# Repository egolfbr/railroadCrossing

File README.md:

# RailRoadCrossing
Arduino based railroad crossing replica 
## Table of Contents
## Table of Contents
**[Introduction](#Introduction)**<br>
**[Gather Materials](#Gather-Matierals)**<br>
**[Building](#Building)**<br>
**[Programming](#Programming)**<br>
**[Conclusion](#Conclusion)**<br>

## Introduction
With the coronavirus sending students home for the rest of the semester (spring 2020), I found myself with a lot of extra time on my hands and lots of parts that I have never used.I recalled that the theme for this years VBS at my church is a railroad theme and my idea was born. I decided that I was going to make a railroad crossing signal. You know the ones with the moving arm, sound and blinking lights. It seemed a little easy especially since I am a junior electrical engineering student so I set off to work, needless to say, I encountered many errors and problems that made this a not an “easy” project. Certainly not a “plug and go” anyway lets get started.

## Gather Materials
Step 1: Gather materials. 
* 3x Arduino UNOs - $23/ea (arduino.cc)
* 2x microswitches - $2/ea* (microcenter)
* 2x pushbuttons - $0.10/ea (digikey)
* 2x 8Ohm-1W speakers - $2.95/ea (microcenter)
* 1x adafruit sound effects board $30/ea (adafruit)
* 2x neopixel ring (16LEDs)
* 1x barrel jack
* 1x 5V 3A power supply
* 2x 10K ohm resistors
* Jumper wire
* 2x MOSFET N-ch 30V transistor
* 2x MOSFET P-ch 27A transistor
* 1x 555 timer
* 1x 125V 3A fuse
* 2x 10000pf ceramic capacitor
* 2x 1n4004 diode
* 1x 19rpm economy brush pur motor
* 1x 4mm shaft mount 32 pitch 16T gear
* 1x 32 pitch 64T 1” bore gear

Estimated total cost:
	For those who do not have any previous material the estimated total cost is about $276. This does not include shipping and tax as you will most likely end up ordering from multiple different places. Websites such as Amazon may make it cheaper. I ended up spending just under $100 on parts that I didn’t have. PCB ordering is also not factored into this cost. I usually order PCBs from China. This means that I have to order a minimum of 10 boards per design. Thus with SeedStudio, I will have to pay around $5 for each design as well as shipping and tax for each one. I also included what the cost would be had I been contracted by a client to build this device. I used a simple google search of the median income of an electrical engineer to base my calculation for the per hour pay. 

You may be wondering why I use so many microcontrollers for a relatively simple process. I was limited by 2 main factors in this build, materials that I had, and money. Now, using 3 micro controllers seems like a costly thing to do and it is. However, I was lucky enough to receive a donation of parts last year which included about 10 arduinos. So having these extra controllers was a huge relief because it allowed me to make this project more parallel. In other words, I have multiple processes running at the same time across multiple devices. I will get into this more as I explain the circuit in the next section, but as some of you may guess, running certain processes takes time and if I want to say blink LEDs and move a motor at the same time, there will be a delay in the circuit. I may make a video example of what I am talking about for those who are confused. 
## Building 
Step 2: build the circuit.
	The most important thing to remember here is to CONNECT ALL GROUND PINS. Also pin numbers are arbitrary. There is no specific reason I choose any of the digital IO pins. The SDA and SCL pins however must remain on A4 and A5 respectively. There are other places to connect these pins on other versions of the arduino UNO but I like to use these pins because they are universal on the UNO models. 
	Additionally, due to my lack of knowledge in EAGLE I will attach hand drawn circuit schematics for parts of the circuit that parts aren’t readily available for on EAGLE so that you have them and I will work on updating the EAGLE file so that there is one complete schematic file that can be downloaded. On the hand-drawn circuits, any node names that are the same on the EAGLE file are connected. For example, on the board labeled SOUND, there is a pin labeled SOUNDPIN. On the hand-drawn schematic there is also a SOUNDPIN, that means that those nodes are connected. Also there is a portion of the circuit that is simplified. For the neopixel rings I only included 2xsingle LED schematics. In reality each of those single LEDs is a whole 16 LED ring. Connections are the same though because you are connecting the last LED on the first ring with the first LED on the second ring.
	So like I mentioned before, I chose to use multiple arduino so that I could make this a parallel design. The other option for me would be to use an FPGA since those are much easier to parallelize however, I did not have the equipment to debug that device. So that is why I ended up with lots of arduinos. First I was planning on just using two arduinos but found that trying to quickly change cases in the state machine (the code implementation that I will discuss next), this proved too slow. This is because in the code I called a function to flash the neopixel LEDs and this takes time. 
Let me take a break here and explain why I chose neopixel rings. Realistically I would’ve used lots of small 3-5mm LEDs and not these rings. That is because with the single diodes, you can simply connect and disconnect power to blink the LEDs. This would lead me to do a hardware implementation of the blinking lights. This can be done a couple ways. I saw a way to do it with a switching NPN transistor similar to the 2n2222 (please correct me if I am wrong). I imagine that this can be done with a crystal oscillator or a 555 timer circuit. I did have several 555 timers available to use but unfortunately I only had about 20 THT LEDs. So that is the main reason that I used the rings. I also find the rings brighter. The big downside is that they must remain plugged into the programmed pin (in my case pin 6). 
Okay so I grabbed a new arduino so that I could put a dedicated LED flashing code on it to flash during 3 of the 4 states of the state machine. Even though this one arduino is slower than the rest in terms of reading/displaying data on the SDA line, it is more acceptable because little kids love LEDs and who cares if the LEDs are on for a second or 2 longer than necessary. It is much more desirable and safer than say having the master arudino not read the digital pins while the motor is still running trying to push the arm higher and stalling the motor and maybe causing a fire. 
For the sound arduino I used the Adafruit sound effects board and some low powered speakers. This was the plug and go part of the project. There is a tutorial on how to use this board on Adafruit’s website which I will post a link to. The sound file is a simple MP3 that I downloaded for free (link below). You don’t have to include a sound portion to this project as it does get rather annoying but I always enjoy sound effects.
For the motor I just used the sound arduino because the sound doesn’t take a lot of time because it is just toggling a pin high and low. I used an attached link for the build of a custom H-bridge motor driver with variable speed and direction. The attached link had 95% of the circuit already designed so that was very helpful. The only portion that I personally designed and built was making it “programmable.” This means that instead of using a physical switch to change direction and to power the motor on and off, I used signals from the arduino dedicated to that function. The main issue is that I needed a SPDT switch that doesn’t require human interaction. Again, limited by supplies I landed on a 5V relay. A relay can be used similar to a 2n2222 transistor in that it can control higher voltage and amperage signals with a common 5V or 3.3V signal depending on the relay. In this case I didn’t need it to control a high voltage or current, just the fact that I needed it to be programmable. So the relay portion of the circuit controls the direction because for an H-bridge, if one side is connected to the power supply, and the other side is at ground, then the motor spins one way and if you switch those signals then you can make it spin the other way. To control the status of the motor (whether it is on or off) I simply used another N-Channel MOSFET transistor. Below are some images of the full circuit. First is the full motor dirver all wired up with a PWM signal and Hbridge, then just the PWM signal generator (555 timer circuit), then the master controller which takes inputs from sensors and buttons, the LED circuit which is just some neoPixel Rings, and finally, the audio circuit. I used an Adafruit sound effects board to shorten the project and bring the complexity down a bit.
<p align="center">

<p align="center">

<p align="center">

<p align="center">

<p align="center">

## Programming
Step 3: Code the Arduino’s
	For this project I implemented a state machine. This is just so that it is easier to organize on paper, in the code and in my head. Basically a state machine is a machine whose outputs are decided by which state it is in and the state is decided by the inputs. That is just a very general description. State machines are all around us from traffic lights to elevators, so it is very useful to get to know how to program one and how they work. Typically, these are implemented with an FPGA but they can really be implemented with anything. My code is heavily commented so I don’t anticipate this to be a long section. 

State Diagram:

<p align="center">

The state diagram helps visualize what is supposed to happen. This helps when errors occur etc.  
A key note that I found out debugging my code is that the break statements are very important when using switch statements. Without these the code won’t run properly. I tried to do some basic research on the switch statements because I had used switch statements before but I had not looked into why we use breaks. What I came up with was that breaks basically prevent the code from running the following case.

## Conclusion

Overall this project took me about 12 hours to complete. I worked for about 2-3 hrs every couple days or so for about 3 weeks. However, if you had all the parts I imagine that this would take maybe an afternoon or two. The main thing that slowed me down were simple software errors mainly. The hardware was rather simple once I got the parts. There were a few instances where I had to improvise and come up with some of my own stuff (see motor power and motor direction without buttons) but again most of the information was already available I just had to synthesize it in a certain way. If I were to do this again  I would try to implement this with an FPGA and more hardware solutions like the 555 timer circuit for the LEDs. I would like to print PCBs for this project to make it more professional as well. Furthermore I would like to see if there is a way to use less arduinos. The one thing that I will probably actually do as an extension is that I will add another arduino or raspberry pi to read telemetry data from the circuit and based on that master data determine if it is necessary to shut the circuit off. I already need to wire battery packs to all the arduinos to a master switch to turn them all on  at the same time and having that switch or another controlled via microcontroller shouldn’t be too hard. I will also add a screen to display current information relevant to the well being of the circuit. 
	
video link: https://youtu.be/l8aVLoQLqr0

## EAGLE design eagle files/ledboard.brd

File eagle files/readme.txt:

These files are free software: you can redistribute it and/or modify
    it under the terms of the GNU General Public License as published by
    the Free Software Foundation, either version 3 of the License, or
    (at your option) any later version.

    This program is distributed in the hope that it will be useful,
    but WITHOUT ANY WARRANTY; without even the implied warranty of
    MERCHANTABILITY or FITNESS FOR A PARTICULAR PURPOSE.  See the
    GNU General Public License for more details.

    You should have received a copy of the GNU General Public License
    along with this program.  If not, see <https://www.gnu.org/licenses/>.
    
    These eagle files were prototyped and designed by Brian Egolf.

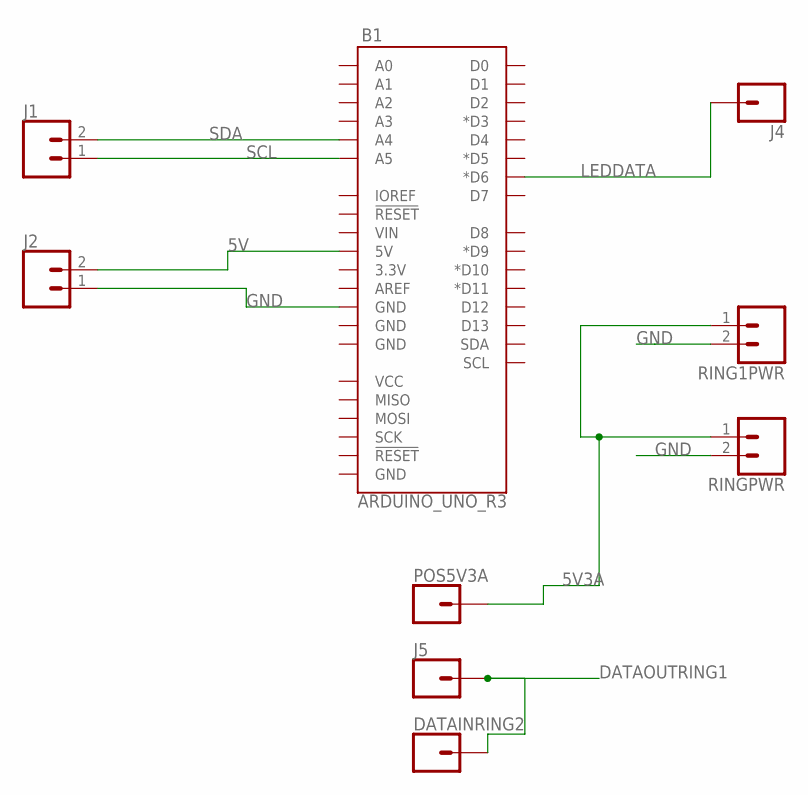
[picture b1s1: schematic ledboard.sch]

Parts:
B1: ARDUINO_UNO_R3; ARDUINO_R3
DATAINRING2: CONN_01; 1X01
J1, J2: CONN_023.5MM; SCREWTERMINAL-3.5MM-2
J4, J5: CONN_01; 1X01
POS5V3A: CONN_01; 1X01
RING1PWR: CONN_023.5MM; SCREWTERMINAL-3.5MM-2
RINGPWR: CONN_023.5MM; SCREWTERMINAL-3.5MM-2

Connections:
5V: B1.5V, J2.2
5V3A: POS5V3A.1, RING1PWR.1, RINGPWR.1
DATAOUTRING1: DATAINRING2.1, J5.1
GND: B1.GND@4 (GND), J2.1, RING1PWR.2, RINGPWR.2
LEDDATA: B1.D6 (*D6), J4.1
SCL: B1.A5, J1.1
SDA: B1.A4, J1.2

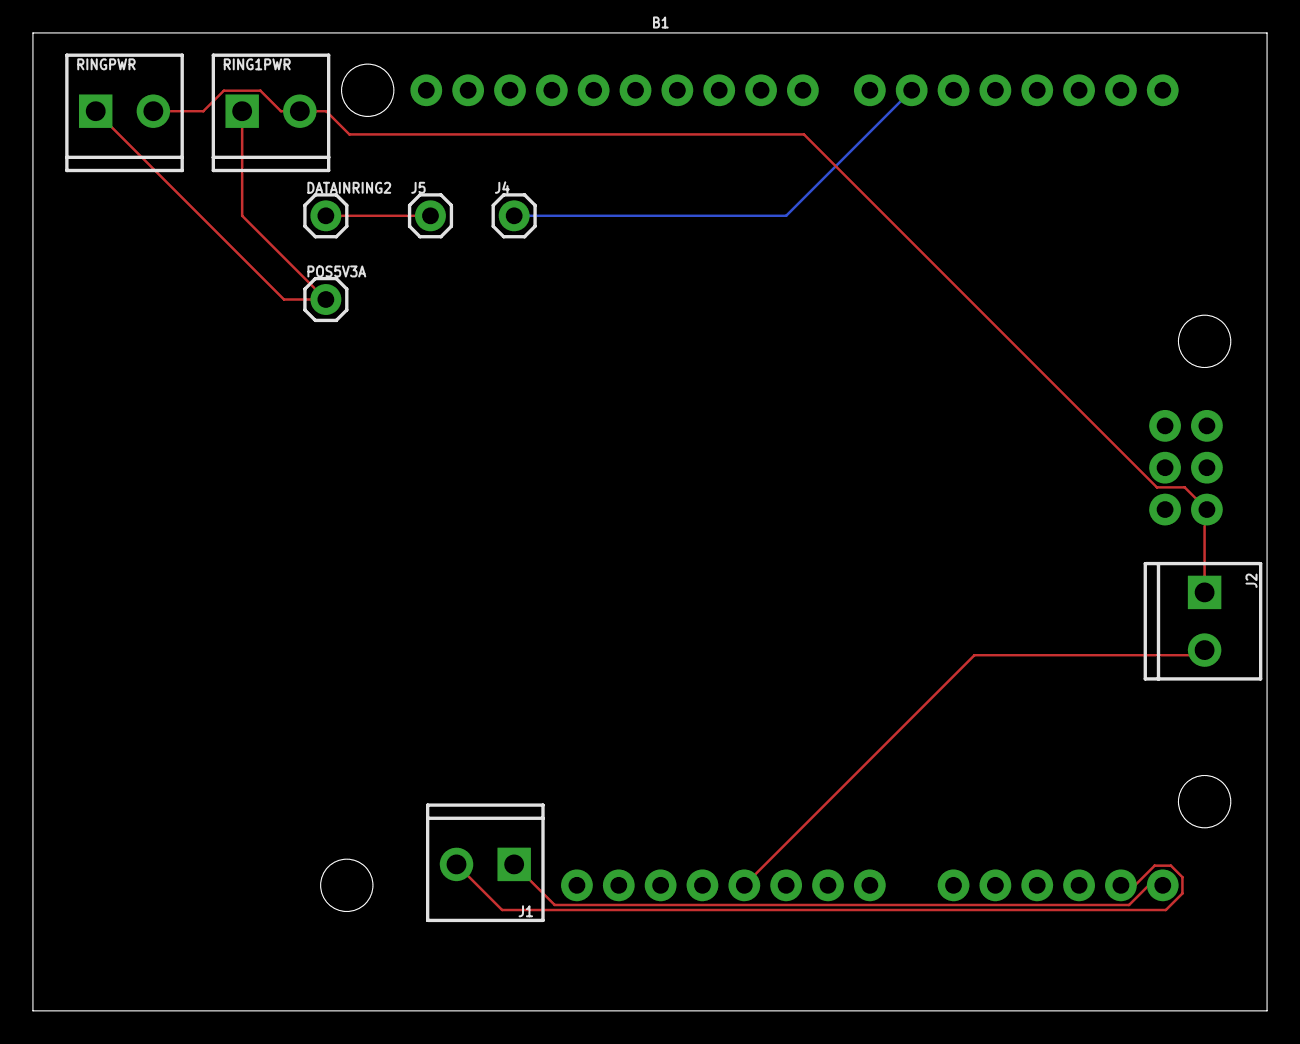
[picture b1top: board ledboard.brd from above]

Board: 2 copper layers, 74.9 x 59.4 mm, 9 parts (0 on the bottom side), 7 nets.

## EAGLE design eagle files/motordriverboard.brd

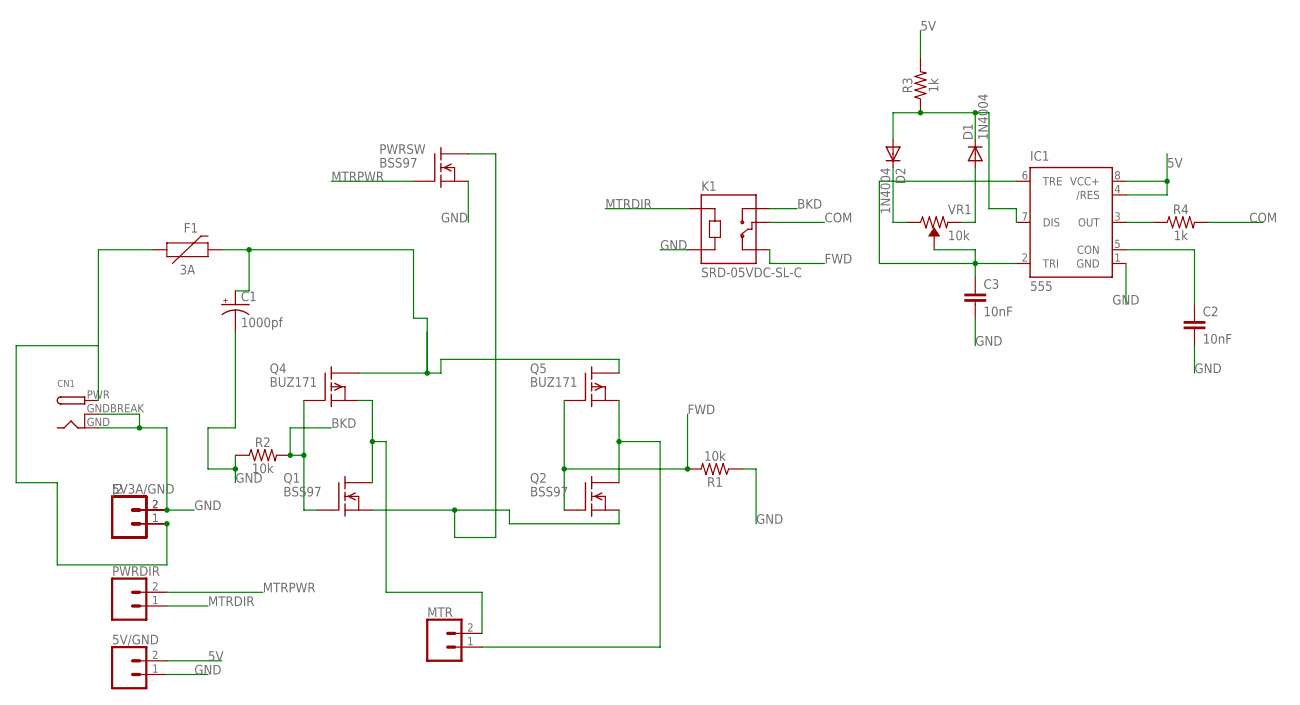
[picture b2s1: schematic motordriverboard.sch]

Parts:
5V3A/GND, 5V/GND: CONN_023.5MM; SCREWTERMINAL-3.5MM-2
C1: 1000pf; E5-6
C2, C3: 10nF; CAP-PTH-10MM
CN1: DCBARRELPTH; DCJACK_2MM_PTH
D1, D2: 1N4004; DO41-10
F1: 3A; PTH
IC1: 555; DIP08
J2: CONN_023.5MM; SCREWTERMINAL-3.5MM-2
K1: SRD-05VDC-SL-C; RELAY_SRD-05VDC-SL-C
MTR: CONN_023.5MM; SCREWTERMINAL-3.5MM-2
PWRDIR: CONN_023.5MM; SCREWTERMINAL-3.5MM-2
PWRSW: BSS97; TO202
Q1, Q2: BSS97; TO202
Q4, Q5: BUZ171; TO220
R1, R2: 10k; AXIAL-0.3
R3, R4: 1k; AXIAL-0.3
VR1: 10k; TRIMPOT-PTH-3386U

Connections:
5V: 5V/GND.2, IC1.4 (/RES), IC1.8 (VCC+), R3.P$2 (2)
BKD: K1.NO, Q1.3 (G), Q4.1 (G), R2.P$2 (2)
COM: K1.COM, R4.P$2 (2)
FWD: K1.NC, Q2.3 (G), Q5.1 (G), R1.P$2 (2)
GND: 5V3A/GND.2, 5V/GND.1, C1.-, C2.2, C3.2, CN1.GND, CN1.GNDBREAK, IC1.1 (GND), J2.2, K1.A2, PWRSW.1 (S), R1.P$1 (1), R2.P$1 (1)
MTRDIR: K1.A1, PWRDIR.1
MTRPWR: PWRDIR.2, PWRSW.3 (G)
unnamed: C2.1, IC1.5 (CON)
unnamed: IC1.3 (OUT), R4.P$1 (1)
unnamed: C3.1, IC1.2 (TRI), IC1.6 (TRE), VR1.2 (WIPER)
unnamed: C1.+, F1.P$2 (2), Q4.2 (D), Q5.2 (D)
unnamed: D1.C, D2.A, IC1.7 (DIS), R3.P$1 (1)
unnamed: MTR.1, Q2.2 (D), Q5.3 (S)
unnamed: MTR.2, Q1.2 (D), Q4.3 (S)
unnamed: PWRSW.2 (D), Q1.1 (S), Q2.1 (S)
unnamed: 5V3A/GND.1, CN1.PWR, F1.P$1 (1), J2.1
unnamed: D2.C, VR1.3 (CW)
unnamed: D1.A, VR1.1 (CCW)

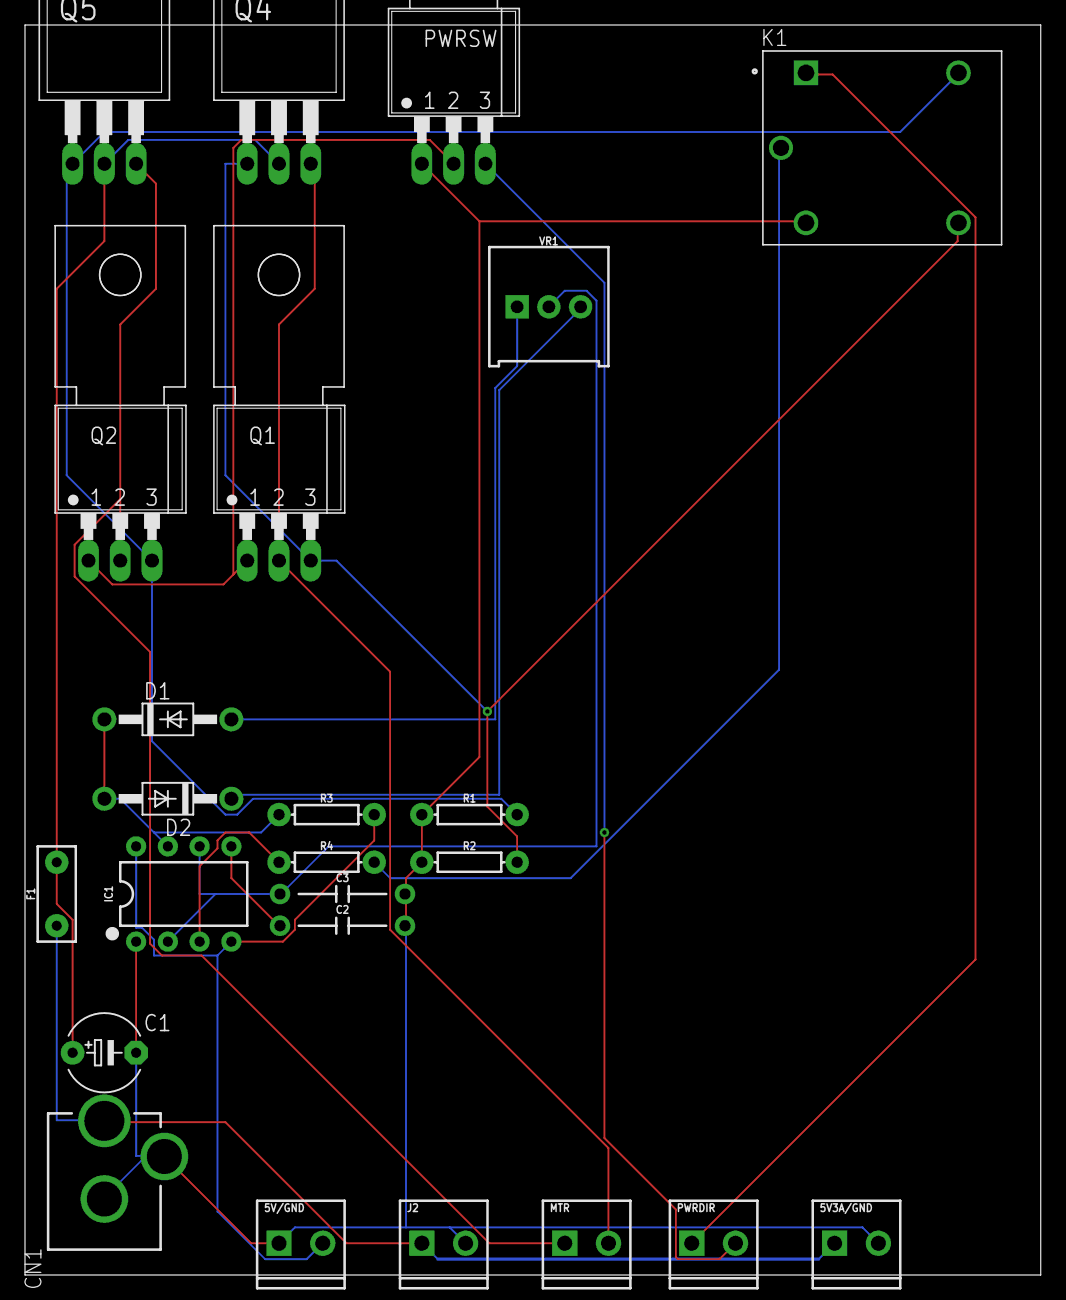
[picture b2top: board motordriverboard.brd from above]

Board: 2 copper layers, 81.3 x 100.0 mm, 24 parts (0 on the bottom side), 18 nets.

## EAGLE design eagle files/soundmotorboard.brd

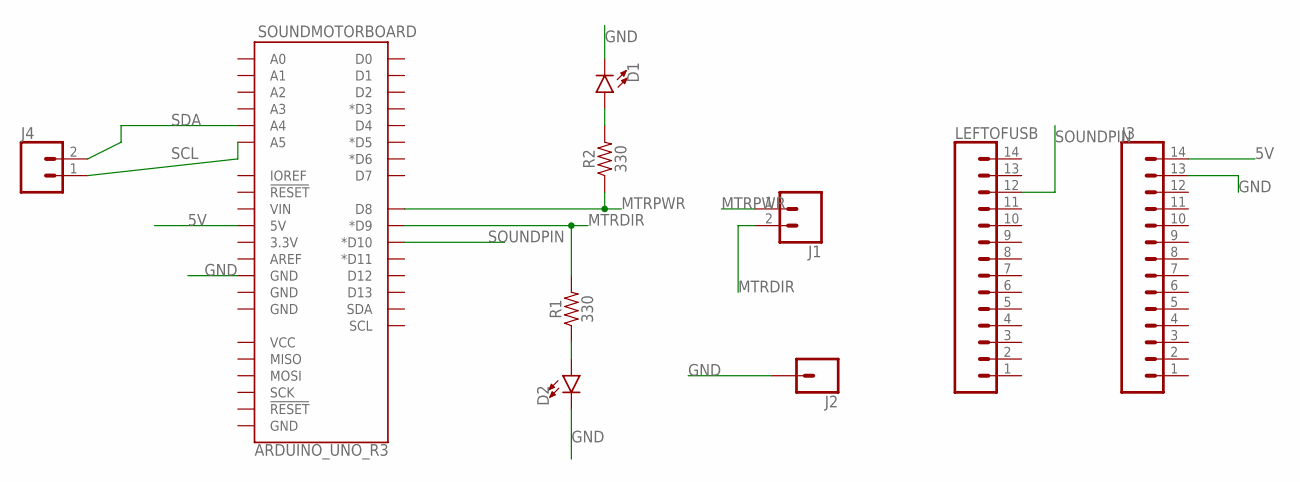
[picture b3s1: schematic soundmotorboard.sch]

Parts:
D1, D2: LED5MM; LED_5MM
J1: CONN_023.5MM-NO_SILK; SCREWTERMINAL-3.5MM-2-NS
J2: CONN_01; 1X01
J3: CONN_14; 1X14
J4: CONN_023.5MM; SCREWTERMINAL-3.5MM-2
LEFTOFUSB: CONN_14; 1X14
R1, R2: 330; AXIAL-0.3
SOUNDMOTORBOARD: ARDUINO_UNO_R3; ARDUINO_R3

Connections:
5V: J3.14, SOUNDMOTORBOARD.5V
GND: D1.K (C), D2.K (C), J2.1, J3.13, SOUNDMOTORBOARD.GND@4 (GND)
MTRDIR: J1.2, R1.P$2 (2), SOUNDMOTORBOARD.D9 (*D9)
MTRPWR: J1.1, R2.P$1 (1), SOUNDMOTORBOARD.D8
unnamed: D1.A, R2.P$2 (2)
unnamed: D2.A, R1.P$1 (1)
SCL: J4.1, SOUNDMOTORBOARD.A5
SDA: J4.2, SOUNDMOTORBOARD.A4
SOUNDPIN: LEFTOFUSB.12, SOUNDMOTORBOARD.D10 (*D10)

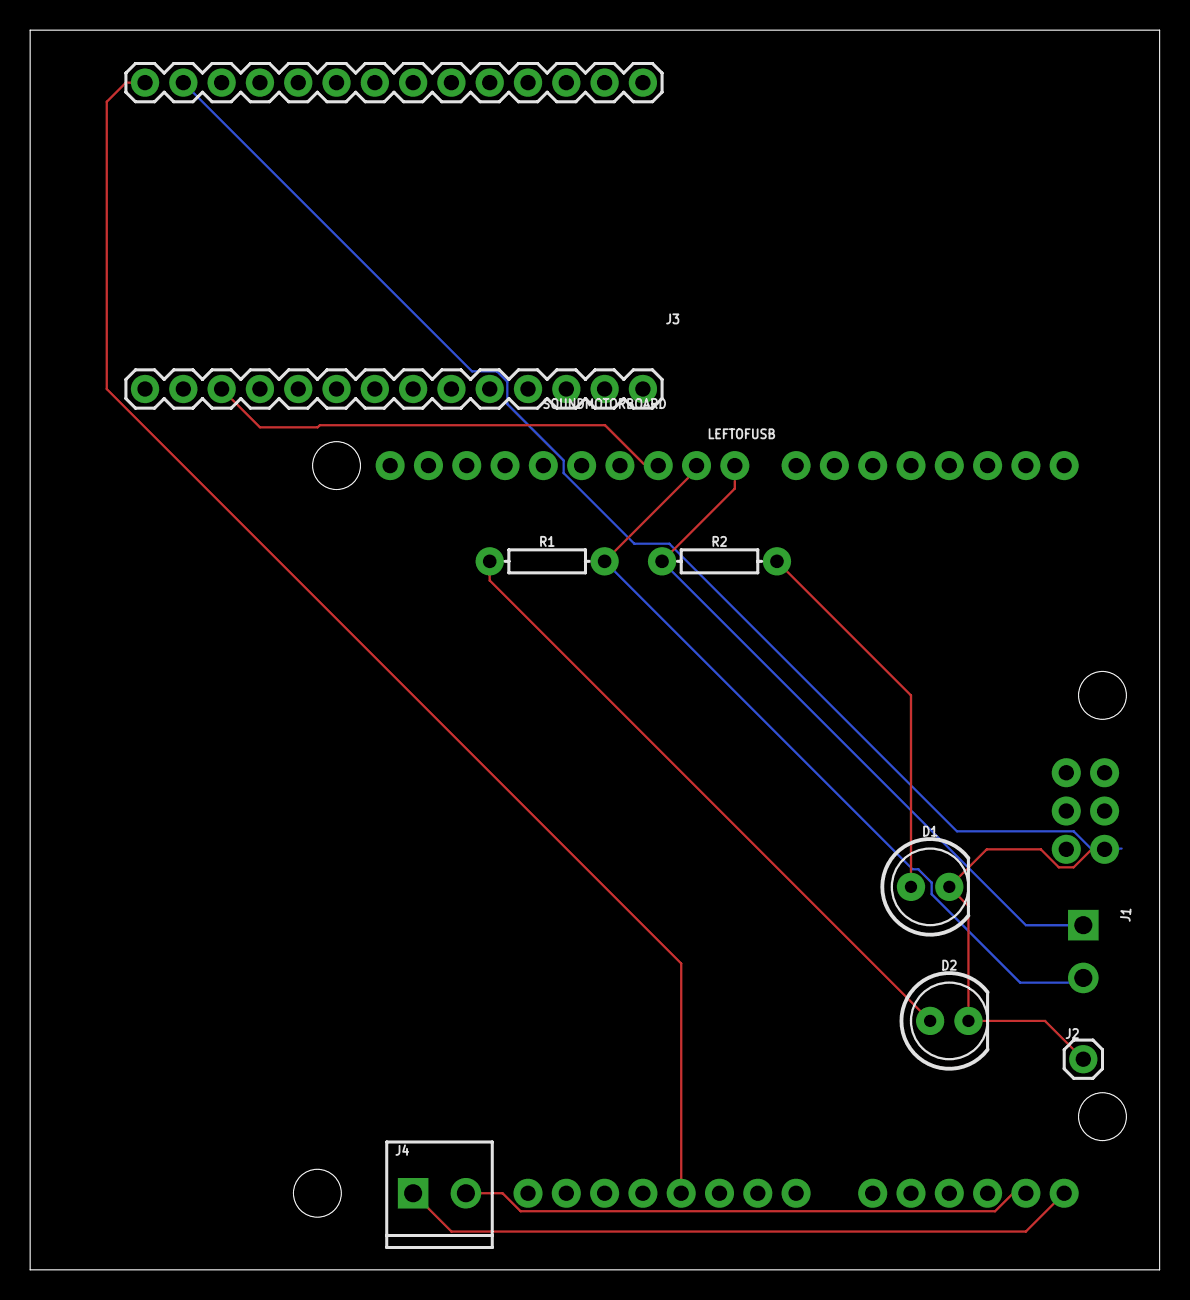
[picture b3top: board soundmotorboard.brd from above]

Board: 2 copper layers, 74.9 x 82.2 mm, 10 parts (0 on the bottom side), 9 nets.

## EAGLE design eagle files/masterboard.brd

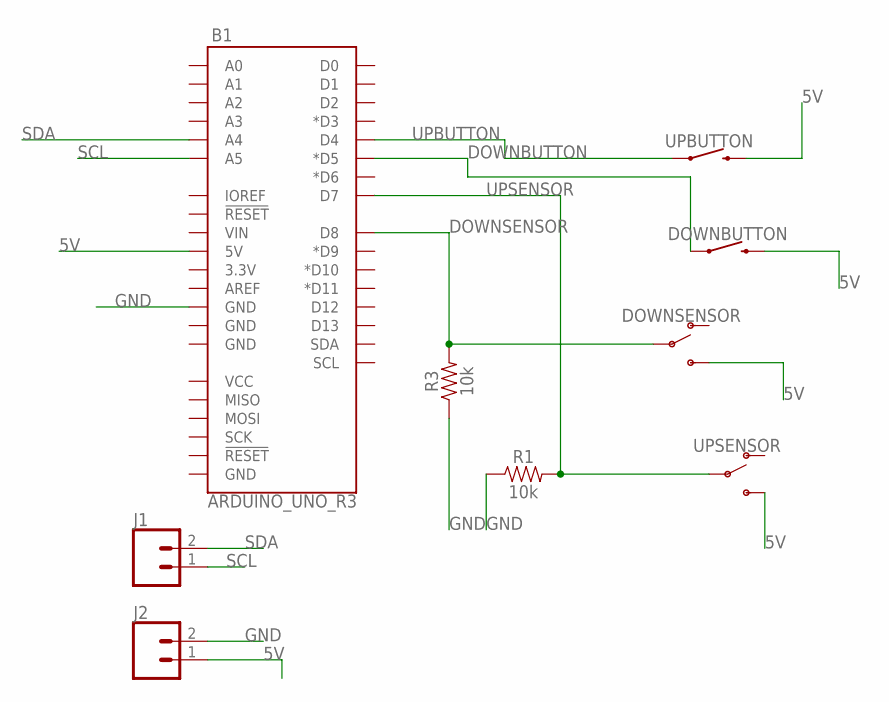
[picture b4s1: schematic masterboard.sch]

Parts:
B1: ARDUINO_UNO_R3; ARDUINO_R3
DOWNBUTTON: MOMENTARY-SWITCH-SPST-PTH-6.0MM-KIT; TACTILE_SWITCH_PTH_6.0MM_KIT
DOWNSENSOR: SWITCH-SPDT-PTH-11.6X4.0MM; SWITCH_SPDT_PTH_11.6X4.0MM
J1, J2: CONN_023.5MM; SCREWTERMINAL-3.5MM-2
R1, R3: 10k; AXIAL-0.3
UPBUTTON: MOMENTARY-SWITCH-SPST-PTH-6.0MM-KIT; TACTILE_SWITCH_PTH_6.0MM_KIT
UPSENSOR: SWITCH-SPDT-PTH-11.6X4.0MM; SWITCH_SPDT_PTH_11.6X4.0MM

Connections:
5V: B1.5V, DOWNBUTTON.3 (2), DOWNSENSOR.3 (S), J2.1, UPBUTTON.3 (2), UPSENSOR.3 (S)
DOWNBUTTON: B1.D5 (*D5), DOWNBUTTON.1
DOWNSENSOR: B1.D8, DOWNSENSOR.2, R3.P$2 (2)
GND: B1.GND@4 (GND), J2.2, R1.P$1 (1), R3.P$1 (1)
SCL: B1.A5, J1.1
SDA: B1.A4, J1.2
UPBUTTON: B1.D4, UPBUTTON.1
UPSENSOR: B1.D7, R1.P$2 (2), UPSENSOR.2

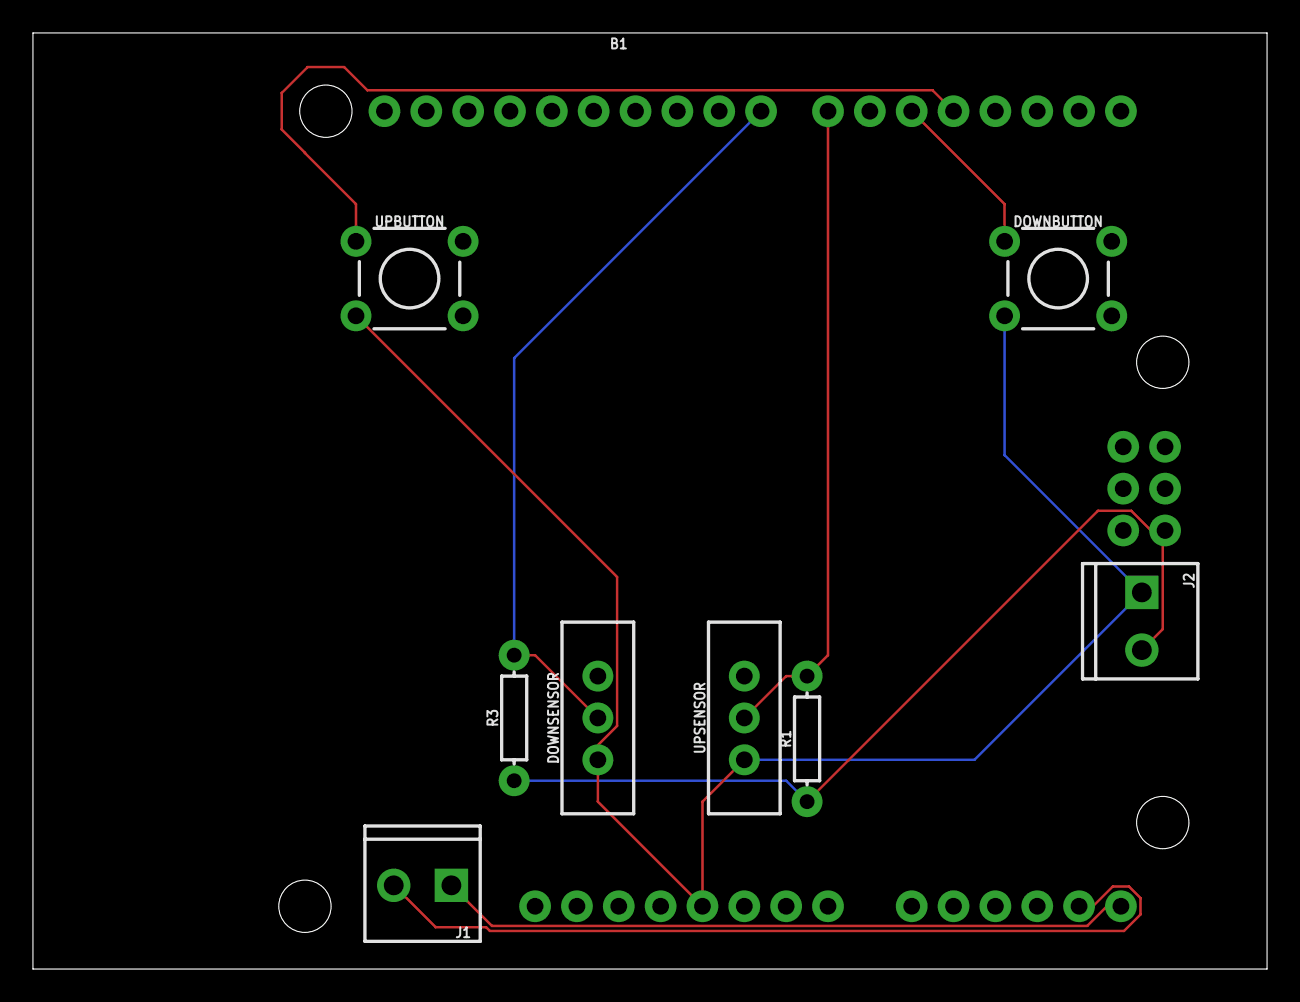
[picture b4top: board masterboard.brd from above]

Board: 2 copper layers, 74.9 x 56.8 mm, 9 parts (0 on the bottom side), 8 nets.

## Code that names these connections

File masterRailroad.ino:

/*
    This program is free software: you can redistribute it and/or modify
    it under the terms of the GNU General Public License as published by
    the Free Software Foundation, either version 3 of the License, or
    (at your option) any later version.

    This program is distributed in the hope that it will be useful,
    but WITHOUT ANY WARRANTY; without even the implied warranty of
    MERCHANTABILITY or FITNESS FOR A PARTICULAR PURPOSE.  See the
    GNU General Public License for more details.

    You should have received a copy of the GNU General Public License
    along with this program.  If not, see <https://www.gnu.org/licenses/>.

*/

//master for the railroad crossing implemented as a state machine

//libraries that this arduino will use in the machine
#include <Wire.h>
#include <Adafruit_NeoPixel.h>

// On a Trinket or Gemma we suggest changing this to 1:
// This is the pin that the DATA_IN pin is connected to on the first ring
#define LED_PIN    6

// How many NeoPixels are attached to the Arduino?
#define LED_COUNT 32

//must declare the strip using the built in declaration statement
Adafruit_NeoPixel strip(LED_COUNT, LED_PIN, NEO_GRB + NEO_KHZ800);

//sensor pins, these are attached to the physical build of the device to sense when the arm is either up or down
int upSensor = 7;
int downSensor = 8;

//buttons for state transition, these will determine if the arm will go up or down depending on which state the machine is in
//for example, if we are in state 0 and the up button is pressed, it won't do anything, but if the down button is pressed then we change states
int upButton = 4;
int downButton = 5;

//vars to store state of the above buttons
int buttonStateUp;
int buttonStateDown;

//comflag to tell if we have already communicated with the other device without a state transition
int comflag = 0;

//to tell the previous states of the machine 
int prevState = 0;

//state var for switch case
int mode = 0;
/*
 * for reference in the switch case here are the following states and the corressponding numbers
 * Start = 0: this is the default start case where the arm is up and the LEDs are off (no train)
 * Move down/flash = 1: this is the state where the arm is moving down and the LEDs are flashing (incoming train)
 * flash (sound?) = 2: this is where the arm has completed its movement and the LEDs are flashing (train is passing)
 * move up/flash = 3: this is the state where the arm moves back up and the LEDs are still flashing
 * 
 * Note: I only commented on the first case since the cases are mostly the same
 */


void setup() {
//begin the I2C communication  protocol
Wire.begin();
//defining the inputs and outputs of the system
pinMode(upButton, INPUT);
pinMode(downButton, INPUT);
pinMode(upSensor, INPUT);
pinMode(downSensor, INPUT);
//begin the serial communication protocol for debugging
Serial.begin(9600);
//start the strip
strip.begin();
strip.show();
}

//byte to send of the I2C communication line
byte x = 0;

void loop() {
//read state of the buttons
  buttonStateDown = digitalRead(downButton);

  //state machine portion. This will determine the output of the I2C data line which will be read by the slave 
  switch(mode) {
    case 0:
    //clear the LEDs 
    clearLeds();
    //tell whether we have communicated with the other boards since we have been in this state
      if(prevState != mode){
        //actually send the data to the slaves
          sendData(mode);
      }

      //determine if the button is pressed
      if(buttonStateDown == HIGH){
        //if the button is pressed then we update the prevState to the current state and then change the mode
        prevState = mode;
        mode = 1;
      }
      else{
        //update the prevState and mode
        prevState = mode;
        mode = 0;
        //switch case will not work properly without this break statement         
       break;
      }
    case 1:
      if(prevState != mode){
          sendData(mode);
      }
      if(digitalRead(downSensor) == HIGH){
        prevState = mode;
        mode = 2;
        
      }
      else{        
        prevState = mode;
        mode = 1;
        break;
      }
    case 2:
     buttonStateUp = digitalRead(upButton);
     if(prevState != mode){
          sendData(mode);
        }
      if(buttonStateUp == HIGH){
        prevState = mode;
        mode = 3;
        
      }
      else{
        
        prevState = mode;
        mode = 2;
        break;
      }
    case 3:
    if(prevState != mode){
          sendData(mode);
    }
    if(digitalRead(upSensor) == HIGH){
      prevState = mode;
      comflag = 0;
      mode = 0;
    }
    else{
      prevState = mode;
      mode = 3;         
      break;
    }
  }

}

void clearLeds(){
   for(int a =0;a<=32;a++){
        strip.setPixelColor(a, strip.Color(0,0,0));
      }
      strip.show();
}

int sendData(byte stateNum){
  //begin wire transmisison to the given address
  Wire.beginTransmission(8);
  //send the state number to the slave
  Wire.write(stateNum);
  //end the transmission
  Wire.endTransmission();
  //begin transmission to the other slave
   Wire.beginTransmission(4);
  Wire.write(stateNum);
  Wire.endTransmission();
  //display when we have sent the data.
  Serial.println("Sent data to slave(s)");
}

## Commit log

2020-04-01 Create LICENSE
2020-04-01 Create eagle files
2020-05-04 Create foo

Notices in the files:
parts and their libraries:
SparkFun-Boards: Licensing: Creative Commons ShareAlike 4.0 International - https://creativecommons.org/licenses/by-sa/4.0
